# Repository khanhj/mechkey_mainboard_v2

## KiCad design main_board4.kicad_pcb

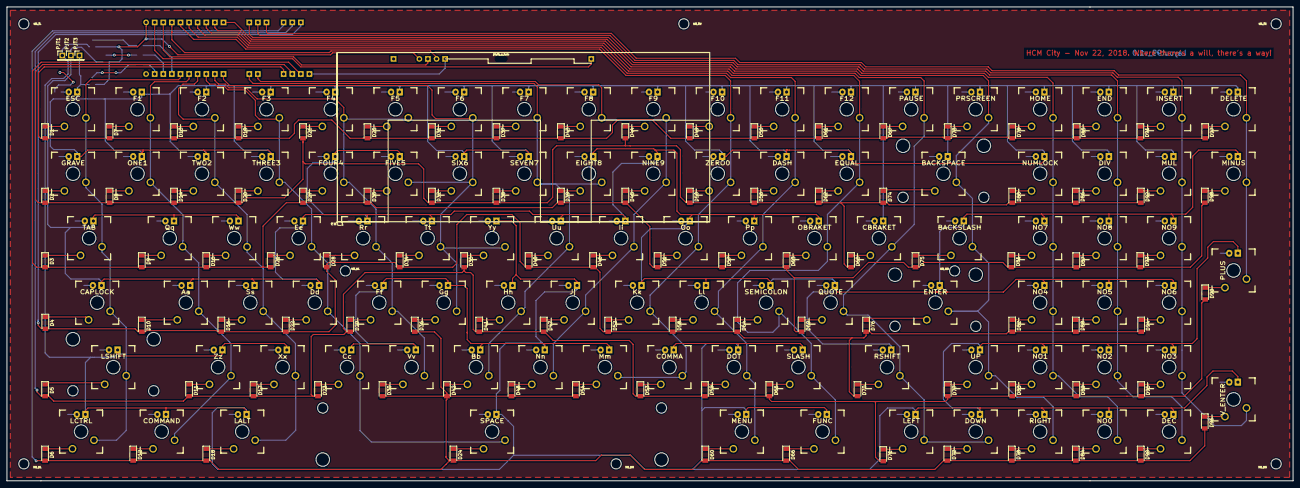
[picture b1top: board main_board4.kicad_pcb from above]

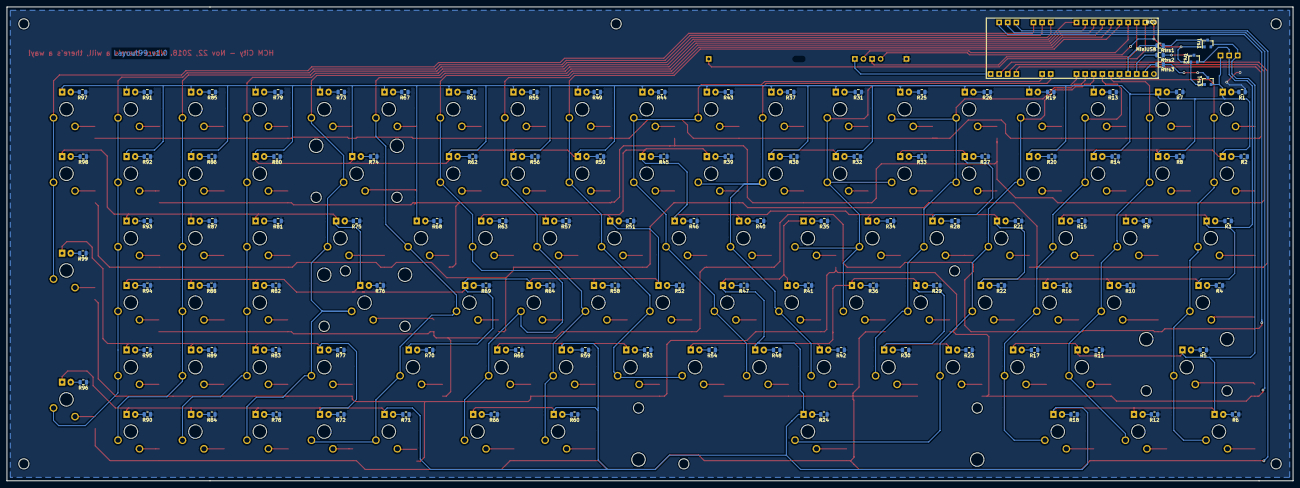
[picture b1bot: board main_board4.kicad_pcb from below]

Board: 2 copper layers, 380.0 x 140.0 mm, 317 parts (106 on the bottom side), 236 nets.

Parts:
Aa: SWITCH_PUSH; CHERRY_PCB_100H
BACKSLASH: SWITCH_PUSH; CHERRY_PCB_150H
BACKSPACE: SWITCH_PUSH; CHERRY_PCB_200H
Bb: SWITCH_PUSH; CHERRY_PCB_100H
CAPLOCK: SWITCH_PUSH; CHERRY_PCB_175H
CBRAKET: SWITCH_PUSH; CHERRY_PCB_100H
COMMA: SWITCH_PUSH; CHERRY_PCB_100H
COMMAND: SWITCH_PUSH; CHERRY_PCB_125H
Cc: SWITCH_PUSH; CHERRY_PCB_100H
D1, D2, D3, D4, D5, D6, D7, D8, D9, D10, D11, D12, D13, D14, D15, D16, D17, D18, D19, D20, D21, D22, D23, D24, D25, D26, D27, D28, D29, D30, D31, D32, D33, D34, D35, D36, D37, D38, D39, D40, D41, D42, D43, D44, D45, D46, D47, D48, D49, D50, D51, D52, D53, D54, D55, D56, D57, D58, D59, D60, D61, D62, D63, D64, D65, D66, D67, D68, D69, D70, D71, D72, D73, D74, D75, D76, D77, D78, D79, D80, D81, D82, D83, D84: DIODE; D_MiniMELFr
D85, D86, D87, D88, D89, D90, D91, D92, D93, D94, D95, D96, D97, D98, D99: DIODE; D_MiniMELF
DASH: SWITCH_PUSH; CHERRY_PCB_100H
DEC: SWITCH_PUSH; CHERRY_PCB_100H
DELETE: SWITCH_PUSH; CHERRY_PCB_100H
DIV: SWITCH_PUSH; CHERRY_PCB_100H
DOT: SWITCH_PUSH; CHERRY_PCB_100H
DOWN: SWITCH_PUSH; CHERRY_PCB_100H
Dd: SWITCH_PUSH; CHERRY_PCB_100H
EIGHT8: SWITCH_PUSH; CHERRY_PCB_100H
END: SWITCH_PUSH; CHERRY_PCB_100H
ENTER: SWITCH_PUSH; CHERRY_PCB_225H
EQUAL: SWITCH_PUSH; CHERRY_PCB_100H
ESC: SWITCH_PUSH; CHERRY_PCB_100H
Ee: SWITCH_PUSH; CHERRY_PCB_100H
F1, F2, F3, F4, F5, F6, F7, F8, F9, F10, F11, F12: SWITCH_PUSH; CHERRY_PCB_100H
FIVE5: SWITCH_PUSH; CHERRY_PCB_100H
FOUR4: SWITCH_PUSH; CHERRY_PCB_100H
FUNC: SWITCH_PUSH; CHERRY_PCB_125H
Ff: SWITCH_PUSH; CHERRY_PCB_100H
GRAVE: SWITCH_PUSH; CHERRY_PCB_100H
Gg: SWITCH_PUSH; CHERRY_PCB_100H
HOME: SWITCH_PUSH; CHERRY_PCB_100H
Hh: SWITCH_PUSH; CHERRY_PCB_100H
INSERT: SWITCH_PUSH; CHERRY_PCB_100H
Ii: SWITCH_PUSH; CHERRY_PCB_100H
Jj: SWITCH_PUSH; CHERRY_PCB_100H
Kk: SWITCH_PUSH; CHERRY_PCB_100H
LALT: SWITCH_PUSH; CHERRY_PCB_125H
LCTRL: SWITCH_PUSH; CHERRY_PCB_125H
LEFT: SWITCH_PUSH; CHERRY_PCB_100H
LSHIFT: SWITCH_PUSH; CHERRY_PCB_225H
Ll: SWITCH_PUSH; CHERRY_PCB_100H
M3_BL, M3_BM, M3_BR, M3_ML, M3_MR, M3_TL, M3_TM, M3_TR: Mounting_hole_M3
MCU: Teensy2.0++; Teensy2.0++_footprint_assigned_v2
MENU: SWITCH_PUSH; CHERRY_PCB_125H
MINUS: SWITCH_PUSH; CHERRY_PCB_100H
MUL: SWITCH_PUSH; CHERRY_PCB_100H
Mm: SWITCH_PUSH; CHERRY_PCB_100H
NINE9: SWITCH_PUSH; CHERRY_PCB_100H
NO0, NO1, NO2, NO3, NO4, NO5, NO6, NO7, NO8, NO9: SWITCH_PUSH; CHERRY_PCB_100H
NUMLOCK: SWITCH_PUSH; CHERRY_PCB_100H
Nn: SWITCH_PUSH; CHERRY_PCB_100H
OBRAKET: SWITCH_PUSH; CHERRY_PCB_100H
ONE1: SWITCH_PUSH; CHERRY_PCB_100H
Oo: SWITCH_PUSH; CHERRY_PCB_100H
PAUSE: SWITCH_PUSH; CHERRY_PCB_100H
PJT1: CON1; PinHeader_1x01_P2.54mm_Vertical
PJT2: CON2; PinHeader_1x01_P2.54mm_Vertical
PJT3: CON3; PinHeader_1x01_P2.54mm_Vertical
PLUS: SWITCH_PUSH; CHERRY_PCB_200V
PRSCREEN: SWITCH_PUSH; CHERRY_PCB_100H
Pp: SWITCH_PUSH; CHERRY_PCB_100H
QUOTE: SWITCH_PUSH; CHERRY_PCB_100H
Qq: SWITCH_PUSH; CHERRY_PCB_100H
R1, R2, R3, R4, R5, R6, R7, R8, R9, R10, R11, R12, R13, R14, R15, R16, R17, R18, R19, R20, R21, R22, R23, R24, R25, R26, R27, R28, R29, R30, R31, R32, R33, R34, R35, R36, R37, R38, R39, R40, R41, R42, R43, R44, R45, R46, R47, R48, R49, R50, R51, R52, R53, R54, R55, R56, R57, R58, R59, R60, R61, R62, R63, R64, R65, R66, R67, R68, R69, R70, R71, R72, R73, R74, R75, R76, R77, R78, R79, R80, R81, R82, R83, R84, R85, R86, R87, R88, R89, R90, R91, R92, R93, R94, R95, R96, R97, R98, R99: R; R_0805_2012Metric
RIGHT: SWITCH_PUSH; CHERRY_PCB_100H
RSHIFT: SWITCH_PUSH; CHERRY_PCB_175H
Rr: SWITCH_PUSH; CHERRY_PCB_100H
Rtrs1, Rtrs2, Rtrs3: R; R_0805_2012Metric
SEMICOLON: SWITCH_PUSH; CHERRY_PCB_100H
SEVEN7: SWITCH_PUSH; CHERRY_PCB_100H
SIX6: SWITCH_PUSH; CHERRY_PCB_100H
SLASH: SWITCH_PUSH; CHERRY_PCB_100H
SPACE: SWITCH_PUSH; CHERRY_PCB_650H
Ss: SWITCH_PUSH; CHERRY_PCB_100H
TAB: SWITCH_PUSH; CHERRY_PCB_150H
THREE3: SWITCH_PUSH; CHERRY_PCB_100H
TWO2: SWITCH_PUSH; CHERRY_PCB_100H
Trs1, Trs2, Trs3: 2SC1815; SOT-23
Tt: SWITCH_PUSH; CHERRY_PCB_100H
UP: SWITCH_PUSH; CHERRY_PCB_100H
Uu: SWITCH_PUSH; CHERRY_PCB_100H
V_ENTER: SWITCH_PUSH; CHERRY_PCB_200V
Vv: SWITCH_PUSH; CHERRY_PCB_100H
Ww: SWITCH_PUSH; CHERRY_PCB_100H
Xx: SWITCH_PUSH; CHERRY_PCB_100H
Yy: SWITCH_PUSH; CHERRY_PCB_100H
ZERO0: SWITCH_PUSH; CHERRY_PCB_100H
Zz: SWITCH_PUSH; CHERRY_PCB_100H
ext_1: ext_module_comp; ext_module_footprint_v2
photo_r_hole: Photo_resistor_hole

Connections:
/LED_C1: BACKSPACE.4, CBRAKET.4, DASH.4, DELETE.4, DIV.4, END.4, EQUAL.4, ESC.4, F1.4, F2.4, F3.4, F4.4, F5.4, F6.4, F7.4, F8.4, F9.4, F10.4, F11.4, F12.4, GRAVE.4, HOME.4, INSERT.4, MUL.4, NUMLOCK.4, ONE1.4, PAUSE.4, PJT3.1, PRSCREEN.4, SEVEN7.4, SIX6.4, THREE3.4, TWO2.4, Trs3.2, ZERO0.4
/LED_C2: Aa.4, BACKSLASH.4, CAPLOCK.4, Dd.4, EIGHT8.4, ENTER.4, Ee.4, FIVE5.4, FOUR4.4, Ii.4, Kk.4, Ll.4, MINUS.4, NINE9.4, NO4.4, NO5.4, NO6.4, NO7.4, NO8.4, NO9.4, OBRAKET.4, Oo.4, PJT2.1, Pp.4, QUOTE.4, Qq.4, RSHIFT.4, Rr.4, SEMICOLON.4, Ss.4, TAB.4, Trs2.2, Tt.4, Uu.4, Ww.4
/LED_C3: Bb.4, COMMA.4, COMMAND.4, Cc.4, DEC.4, DOT.4, DOWN.4, FUNC.4, Ff.4, Gg.4, Hh.4, Jj.4, LALT.4, LCTRL.4, LEFT.4, LSHIFT.4, MENU.4, Mm.4, NO0.4, NO1.4, NO2.4, NO3.4, Nn.4, PJT1.1, PLUS.4, RIGHT.4, SLASH.4, SPACE.4, Trs1.2, UP.4, V_ENTER.4, Vv.4, Xx.4, Yy.4, Zz.4
/Row_1: D1.2, D7.2, D13.2, D19.2, D25.2, D31.2, D37.2, D43.2, D49.2, D55.2, D61.2, D67.2, D73.2, D79.2, D85.2, D91.2, D97.2, MCU.42
/Row_2: D2.2, D8.2, D14.2, D20.2, D26.2, D32.2, D38.2, D44.2, D50.2, D56.2, D62.2, D68.2, D74.2, D80.2, D86.2, D92.2, MCU.43
/Row_3: D3.2, D9.2, D15.2, D21.2, D27.2, D33.2, D39.2, D45.2, D51.2, D57.2, D63.2, D69.2, D75.2, D81.2, D87.2, D93.2, D98.2, MCU.44
/Row_4: D4.2, D10.2, D16.2, D22.2, D28.2, D34.2, D40.2, D46.2, D52.2, D58.2, D64.2, D70.2, D76.2, D82.2, D88.2, D94.2, MCU.16
/Row_5: D5.2, D11.2, D17.2, D23.2, D29.2, D35.2, D41.2, D47.2, D53.2, D59.2, D65.2, D71.2, D77.2, D83.2, D89.2, D95.2, D99.2, MCU.15
/Row_6: D6.2, D12.2, D18.2, D24.2, D30.2, D36.2, D42.2, D48.2, D54.2, D60.2, D66.2, D72.2, D78.2, D84.2, D90.2, D96.2, MCU.14
unnamed: Aa.1, D10.1
unnamed: Aa.2, COMMAND.2, F1.2, MCU.22, ONE1.2, Qq.2, Zz.2
unnamed: Aa.3, R10.2
unnamed: BACKSLASH.1, D75.1
unnamed: BACKSLASH.2, BACKSPACE.2, ENTER.2, MCU.6, PRSCREEN.2, RIGHT.2, UP.2
unnamed: BACKSLASH.3, R75.2
unnamed: BACKSPACE.1, D74.1
unnamed: BACKSPACE.3, R74.2
unnamed: Bb.1, D42.1
unnamed: Bb.2, EIGHT8.2, F7.2, Hh.2, MCU.38, SEVEN7.2, Uu.2
unnamed: Bb.3, R42.2
unnamed: CAPLOCK.1, D4.1
unnamed: CAPLOCK.2, ESC.2, GRAVE.2, LCTRL.2, LSHIFT.2, MCU.23, TAB.2
unnamed: CAPLOCK.3, R4.2
unnamed: COMMA.1, D53.1
unnamed: COMMA.2, F10.2, Kk.2, MCU.2, Mm.2, Oo.2, ZERO0.2
unnamed: COMMA.3, R53.2
unnamed: COMMAND.1, D12.1
unnamed: COMMAND.3, R12.2
unnamed: Cc.1, D23.1
unnamed: Cc.2, Dd.2, Ee.2, F3.2, MCU.20, SPACE.2, THREE3.2
unnamed: Cc.3, R23.2
unnamed: D1.1, ESC.1
unnamed: D2.1, GRAVE.1
unnamed: D3.1, TAB.1
unnamed: D5.1, LSHIFT.1
unnamed: D6.1, LCTRL.1
unnamed: D7.1, F1.1
unnamed: D8.1, ONE1.1
unnamed: D9.1, Qq.1
unnamed: D11.1, Zz.1
unnamed: D13.1, F2.1
unnamed: D14.1, TWO2.1
unnamed: D15.1, Ww.1
unnamed: D16.1, Ss.1
unnamed: D17.1, Xx.1
unnamed: D18.1, LALT.1
unnamed: D19.1, F3.1
unnamed: D20.1, THREE3.1
unnamed: D21.1, Ee.1
unnamed: D22.1, Dd.1
unnamed: D24.1, SPACE.1
unnamed: D25.1, F5.1
unnamed: D26.1, F4.1
unnamed: D27.1, FOUR4.1
unnamed: D28.1, Rr.1
unnamed: D29.1, Ff.1
unnamed: D30.1, Vv.1
unnamed: D31.1, F6.1
unnamed: D32.1, SIX6.1
unnamed: D33.1, FIVE5.1
unnamed: D34.1, Tt.1
unnamed: D35.1, Yy.1
unnamed: D36.1, Gg.1
unnamed: D37.1, F7.1
unnamed: D38.1, SEVEN7.1
unnamed: D39.1, EIGHT8.1
unnamed: D40.1, Uu.1
unnamed: D41.1, Hh.1
unnamed: D43.1, F8.1
unnamed: D44.1, F9.1
unnamed: D45.1, NINE9.1
unnamed: D46.1, Ii.1
unnamed: D47.1, Jj.1
unnamed: D48.1, Nn.1
unnamed: D49.1, F10.1
unnamed: D50.1, ZERO0.1
unnamed: D51.1, Oo.1
unnamed: D52.1, Kk.1
unnamed: D54.1, Mm.1
unnamed: D55.1, F11.1
unnamed: D56.1, DASH.1
unnamed: D57.1, Pp.1
unnamed: D58.1, Ll.1
unnamed: D59.1, DOT.1
unnamed: D60.1, MENU.1
unnamed: D61.1, F12.1
unnamed: D62.1, EQUAL.1
unnamed: D63.1, OBRAKET.1
unnamed: D64.1, SEMICOLON.1
unnamed: D65.1, SLASH.1
unnamed: D66.1, FUNC.1
unnamed: D67.1, PAUSE.1
unnamed: CBRAKET.1, D68.1
unnamed: D69.1, QUOTE.1
unnamed: D70.1, RSHIFT.1
unnamed: D71.1, LEFT.1
unnamed: D72.1, DOWN.1
unnamed: D73.1, PRSCREEN.1
unnamed: D76.1, ENTER.1
unnamed: D77.1, UP.1
unnamed: D78.1, RIGHT.1
unnamed: D79.1, HOME.1
unnamed: D80.1, NUMLOCK.1
unnamed: D81.1, NO7.1
unnamed: D82.1, NO4.1
unnamed: D83.1, NO1.1
unnamed: D84.1, NO0.1
unnamed: D85.1, END.1
unnamed: D86.1, DIV.1
unnamed: D87.1, NO8.1
unnamed: D88.1, NO5.1
unnamed: D89.1, NO2.1
unnamed: D90.1, DEC.1
unnamed: D91.1, INSERT.1
unnamed: D92.1, MUL.1
unnamed: D93.1, NO9.1
unnamed: D94.1, NO6.1
unnamed: D95.1, NO3.1
unnamed: D96.1, V_ENTER.1
unnamed: D97.1, DELETE.1
unnamed: D98.1, MINUS.1
unnamed: D99.1, PLUS.1
unnamed: DEC.2, DIV.2, END.2, MCU.10, NO2.2, NO5.2, NO8.2
unnamed: DEC.3, R90.2
unnamed: DELETE.2, MCU.12, MINUS.2, PLUS.2
unnamed: DELETE.3, R97.2
unnamed: DIV.3, R86.2
unnamed: DASH.2, DOT.2, F11.2, Ll.2, MCU.3, MENU.2, Pp.2
unnamed: DOT.3, R59.2
unnamed: CBRAKET.2, DOWN.2, LEFT.2, MCU.5, PAUSE.2, QUOTE.2, RSHIFT.2
unnamed: DOWN.3, R72.2
unnamed: Dd.3, R22.2
unnamed: EIGHT8.3, R39.2
unnamed: END.3, R85.2
unnamed: ENTER.3, R76.2
unnamed: EQUAL.2, F12.2, FUNC.2, MCU.4, OBRAKET.2, SEMICOLON.2, SLASH.2
unnamed: EQUAL.3, R62.2
unnamed: ESC.3, R1.2
unnamed: Ee.3, R21.2
unnamed: F1.3, R7.2
unnamed: F2.2, LALT.2, MCU.21, Ss.2, TWO2.2, Ww.2, Xx.2
unnamed: F2.3, R13.2
unnamed: F3.3, R19.2
unnamed: F4.2, F5.2, FOUR4.2, Ff.2, MCU.19, Rr.2, Vv.2
unnamed: F4.3, R26.2
unnamed: F5.3, R25.2
unnamed: F6.2, FIVE5.2, Gg.2, MCU.18, SIX6.2, Tt.2, Yy.2
unnamed: F6.3, R31.2
unnamed: F7.3, R37.2
unnamed: F8.2, F9.2, Ii.2, Jj.2, MCU.39, NINE9.2, Nn.2
unnamed: F8.3, R43.2
unnamed: F9.3, R44.2
unnamed: F10.3, R49.2
unnamed: F11.3, R55.2
unnamed: F12.3, R61.2
unnamed: FIVE5.3, R33.2
unnamed: FOUR4.3, R27.2
unnamed: FUNC.3, R66.2
unnamed: Ff.3, R29.2
unnamed: GRAVE.3, R2.2
unnamed: Gg.3, R36.2
unnamed: HOME.2, MCU.7, NO0.2, NO1.2, NO4.2, NO7.2, NUMLOCK.2
unnamed: HOME.3, R79.2
unnamed: Hh.3, R41.2
unnamed: INSERT.2, MCU.11, MUL.2, NO3.2, NO6.2, NO9.2, V_ENTER.2
unnamed: INSERT.3, R91.2
unnamed: Ii.3, R46.2
unnamed: Jj.3, R47.2
unnamed: Kk.3, R52.2
unnamed: LALT.3, R18.2
unnamed: OBRAKET.3, R63.2
unnamed: LCTRL.3, R6.2
unnamed: LEFT.3, R71.2
unnamed: LSHIFT.3, R5.2
unnamed: Ll.3, R58.2
unnamed: MCU.0, ext_1.5
unnamed: MCU.1, ext_1.6
unnamed: MCU.24, Rtrs1.2
unnamed: MCU.25, Rtrs2.2
unnamed: MCU.26, Rtrs3.2
unnamed: MCU.27, ext_1.8
unnamed: MCU.45, ext_1.7
unnamed: MCU.46, R1.1, R2.1, R3.1, R4.1, R5.1, R6.1, R7.1, R8.1, R9.1, R10.1, R11.1, R12.1, R13.1, R14.1, R15.1, R16.1, R17.1, R18.1, R19.1, R20.1, R21.1, R22.1, R23.1, R24.1, R25.1, R26.1, R27.1, R28.1, R29.1, R30.1, R31.1, R32.1, R33.1, R34.1, R35.1, R36.1, R37.1, R38.1, R39.1, R40.1, R41.1, R42.1, R43.1, R44.1, R45.1, R46.1, R47.1, R48.1, R49.1, R50.1, R51.1, R52.1, R53.1, R54.1, R55.1, R56.1, R57.1, R58.1, R59.1, R60.1, R61.1, R62.1, R63.1, R64.1, R65.1, R66.1, R67.1, R68.1, R69.1, R70.1, R71.1, R72.1, R73.1, R74.1, R75.1, R76.1, R77.1, R78.1, R79.1, R80.1, R81.1, R82.1, R83.1, R84.1, R85.1, R86.1, R87.1, R88.1, R89.1, R90.1, R91.1, R92.1, R93.1, R94.1, R95.1, R96.1, R97.1, R98.1, R99.1, ext_1.1
unnamed: MCU.49, Trs1.1, Trs2.1, Trs3.1, ext_1.4
unnamed: MENU.3, R60.2
unnamed: DASH.3, R56.2
unnamed: MUL.3, R92.2
unnamed: Mm.3, R54.2
unnamed: NINE9.3, R45.2
unnamed: NO0.3, R84.2
unnamed: NO1.3, R83.2
unnamed: NO4.3, R82.2
unnamed: NO7.3, R81.2
unnamed: NUMLOCK.3, R80.2
unnamed: Nn.3, R48.2
unnamed: NO2.3, R89.2
unnamed: NO3.3, R95.2
unnamed: NO5.3, R88.2
unnamed: NO6.3, R94.2
unnamed: NO8.3, R87.2
unnamed: NO9.3, R93.2
unnamed: ONE1.3, R8.2
unnamed: Oo.3, R51.2
unnamed: PAUSE.3, R67.2
unnamed: PLUS.3, R99.2
unnamed: PRSCREEN.3, R73.2
unnamed: Pp.3, R57.2
unnamed: QUOTE.3, R69.2
unnamed: Qq.3, R9.2
unnamed: R3.2, TAB.3
unnamed: R11.2, Zz.3
unnamed: R14.2, TWO2.3
unnamed: R15.2, Ww.3
unnamed: R16.2, Ss.3
unnamed: R17.2, Xx.3
unnamed: R20.2, THREE3.3
unnamed: R24.2, SPACE.3
unnamed: R28.2, Rr.3
unnamed: R30.2, Vv.3
unnamed: R32.2, SIX6.3
unnamed: R34.2, Tt.3
unnamed: R35.2, Yy.3
unnamed: R38.2, SEVEN7.3
unnamed: R40.2, Uu.3
unnamed: R50.2, ZERO0.3
unnamed: R64.2, SEMICOLON.3
unnamed: R65.2, SLASH.3
unnamed: CBRAKET.3, R68.2
unnamed: R70.2, RSHIFT.3
unnamed: R77.2, UP.3
unnamed: R78.2, RIGHT.3
unnamed: R96.2, V_ENTER.3
unnamed: MINUS.3, R98.2
unnamed: Rtrs1.1, Trs1.3
unnamed: Rtrs2.1, Trs2.3
unnamed: Rtrs3.1, Trs3.3

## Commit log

2018-11-12 update layout
2018-11-12 update sche
2018-11-13 update wiring
2018-11-13 wiring completed
2018-11-14 add new footprint
2018-11-15 keep old pcb design
2018-11-17 align key
2018-11-17 wiring led
2018-11-18 wring controller
2018-11-18 modify ext module
2018-11-19 working on trans
2018-11-20 done
2018-11-20 align text
2018-11-21 adding mounthole
2018-11-21 adjust mounting hole
2018-11-22 decoration
2018-11-22 export gerber
2018-11-22 add plate
2018-11-23 looking at plate
